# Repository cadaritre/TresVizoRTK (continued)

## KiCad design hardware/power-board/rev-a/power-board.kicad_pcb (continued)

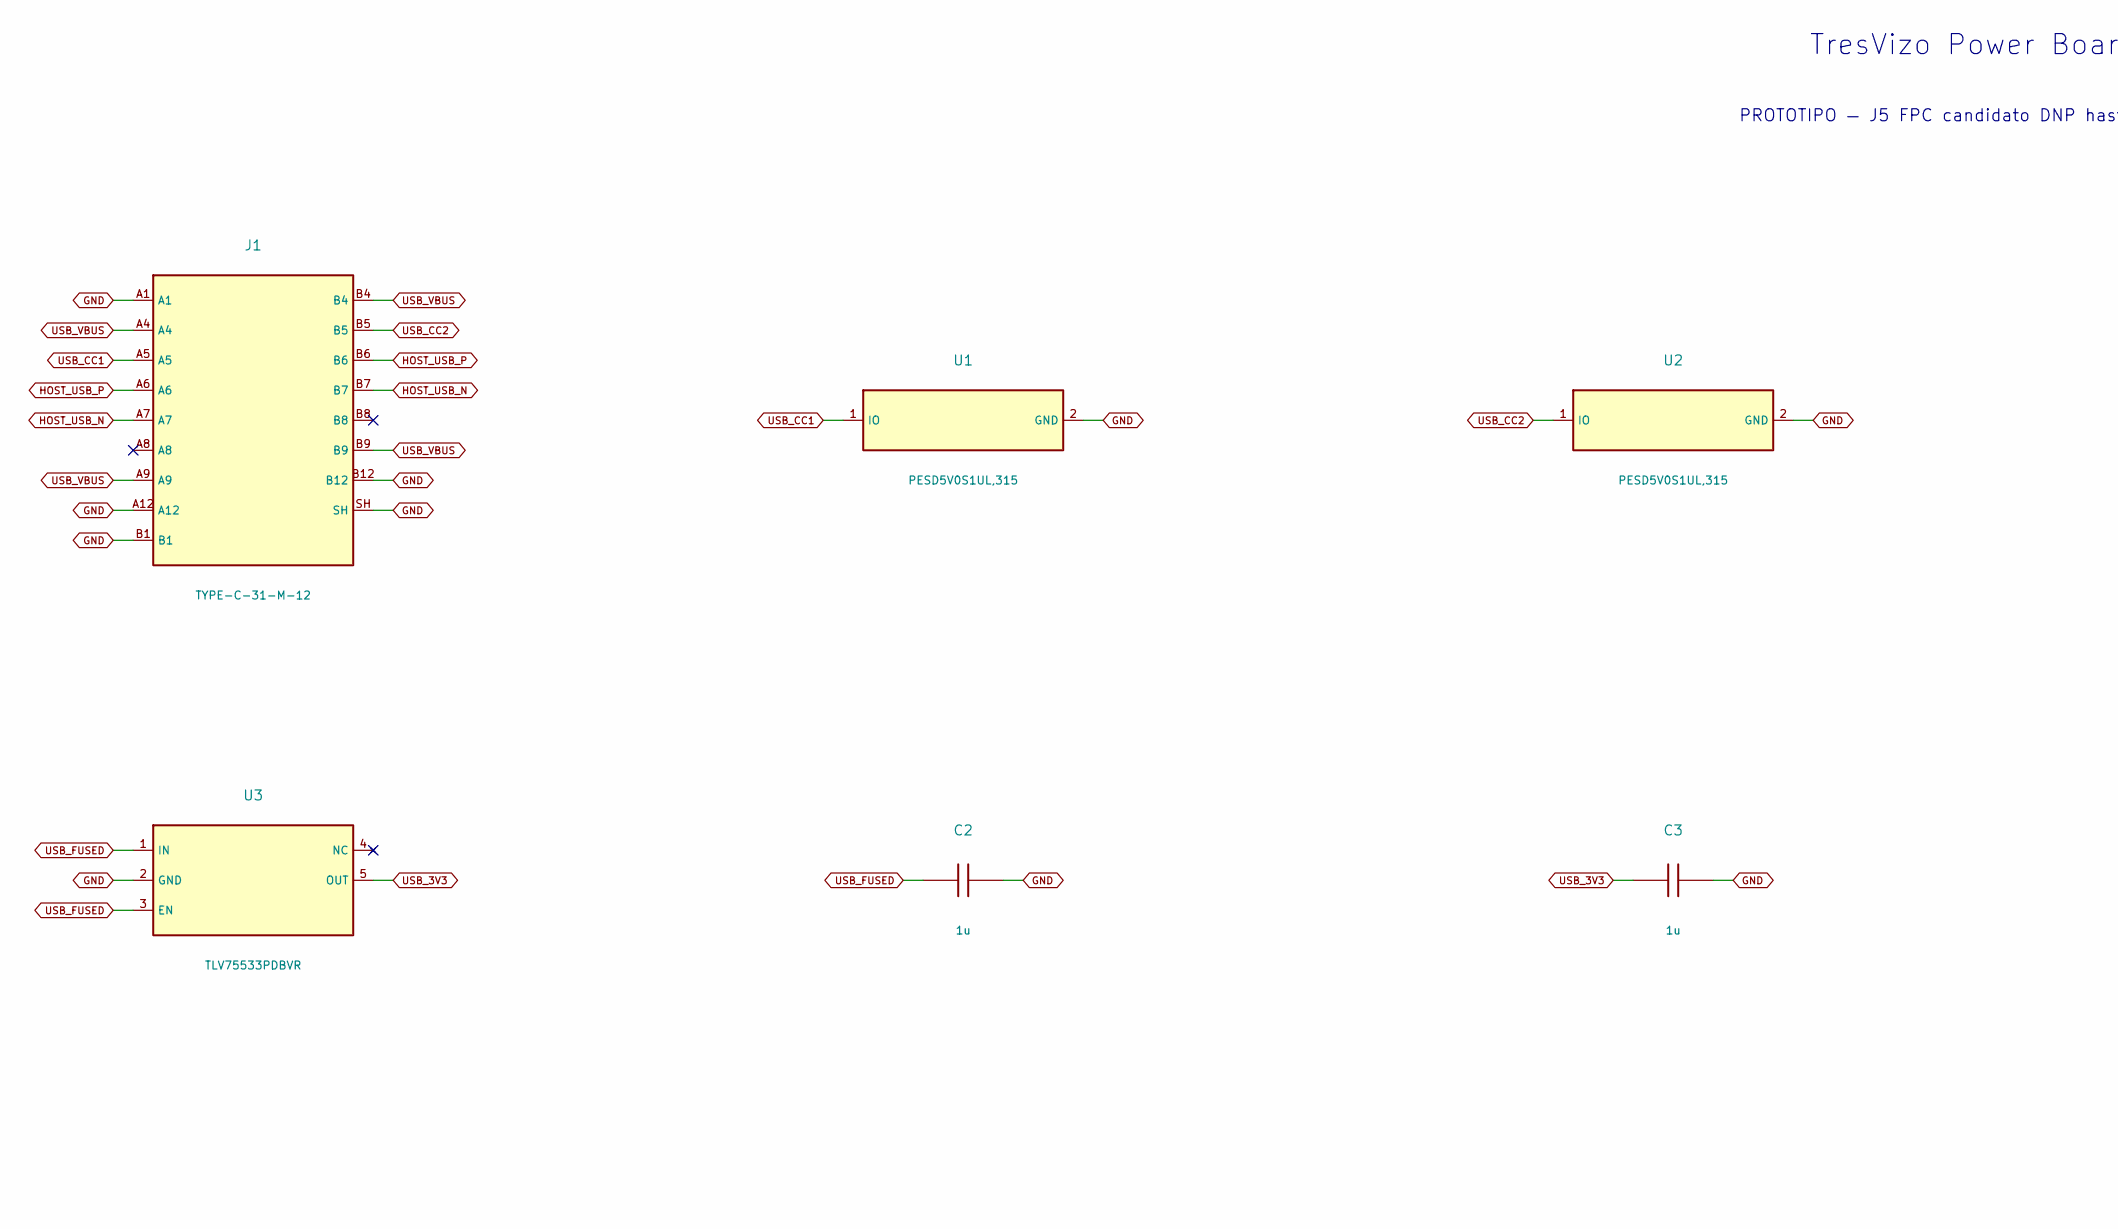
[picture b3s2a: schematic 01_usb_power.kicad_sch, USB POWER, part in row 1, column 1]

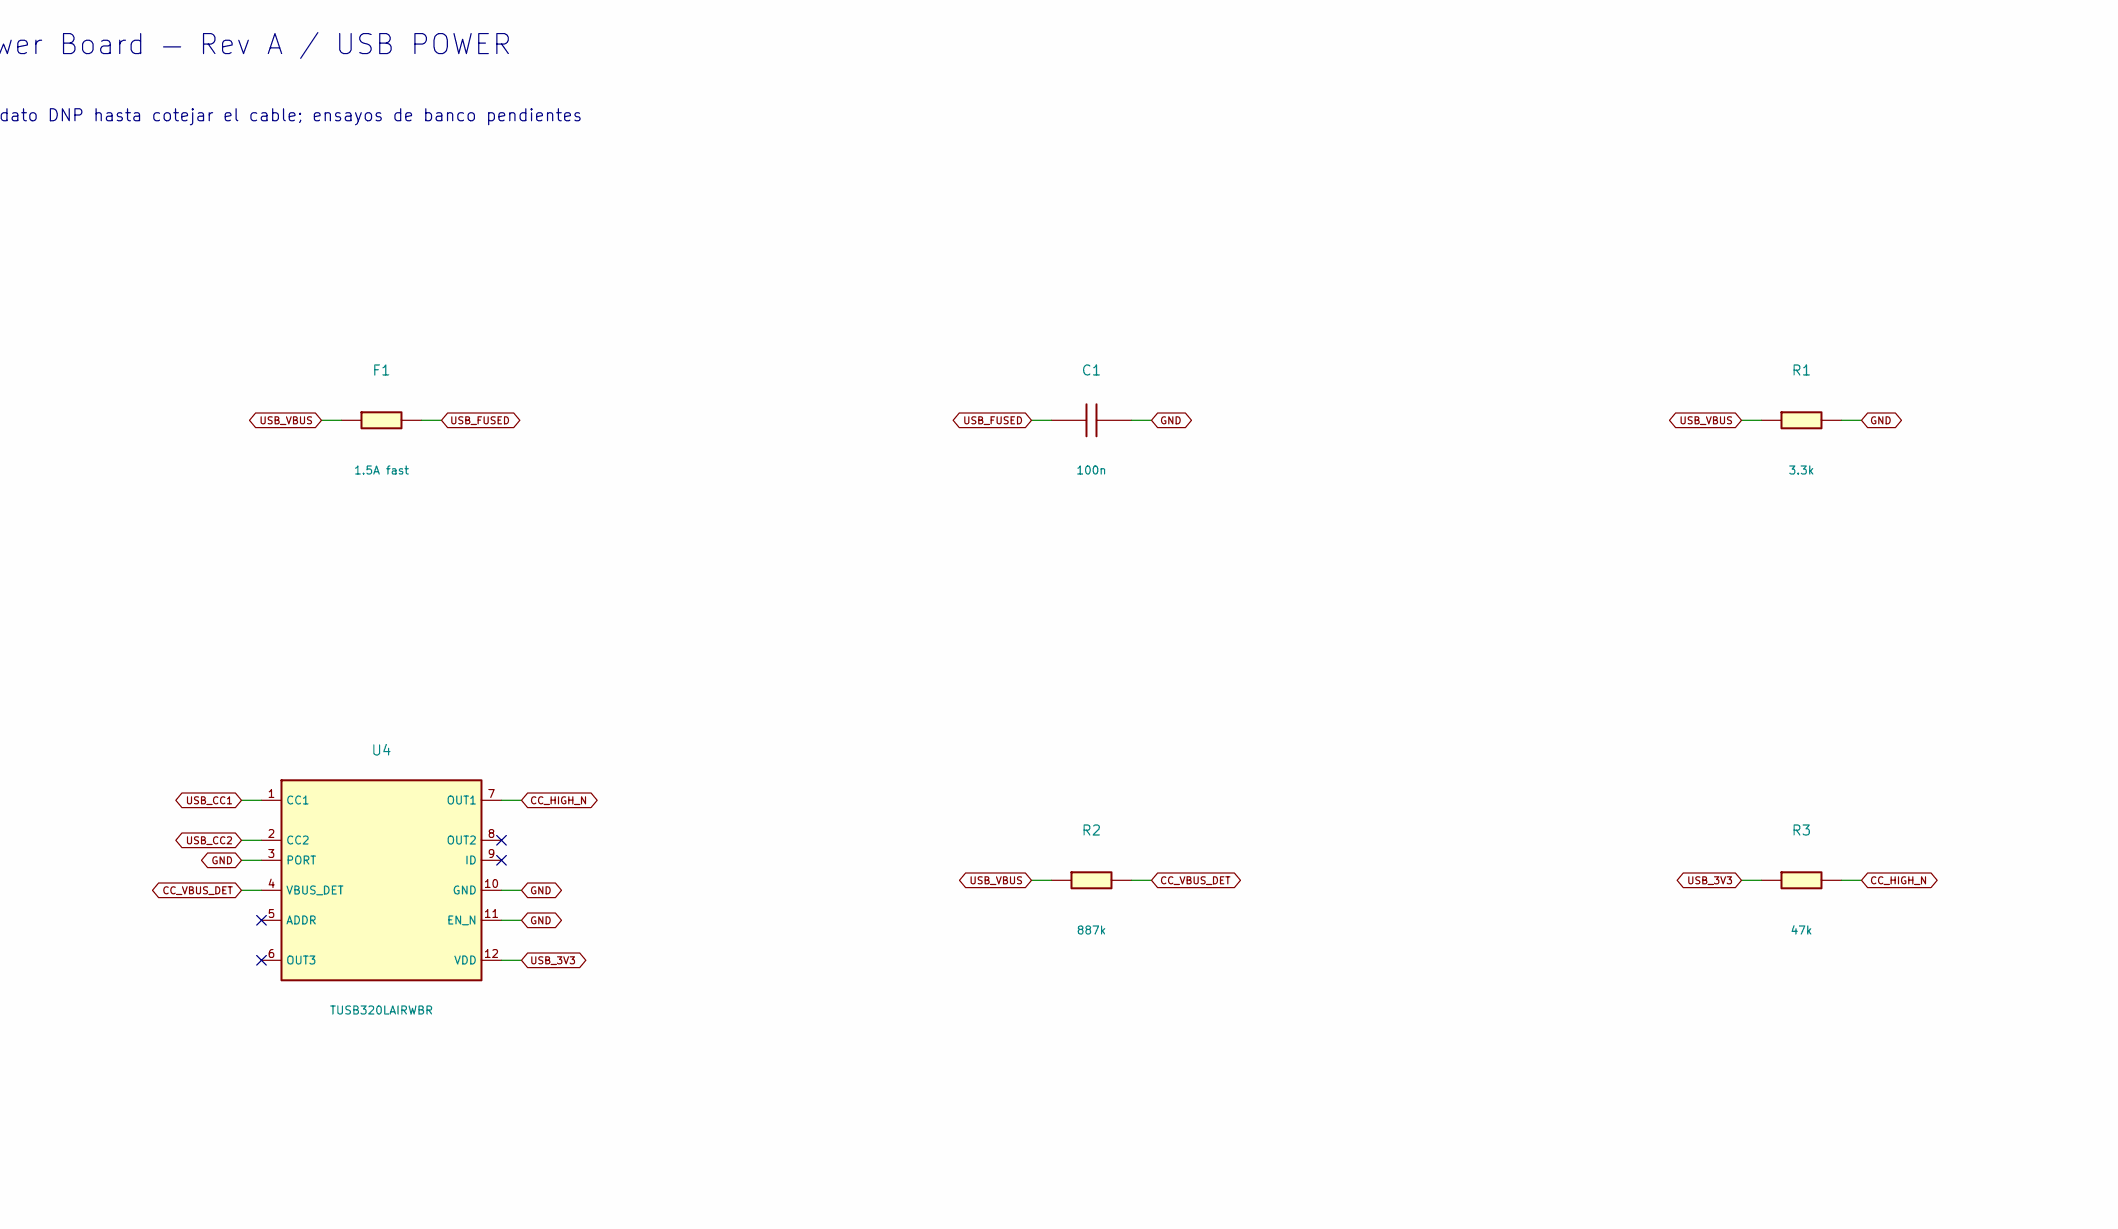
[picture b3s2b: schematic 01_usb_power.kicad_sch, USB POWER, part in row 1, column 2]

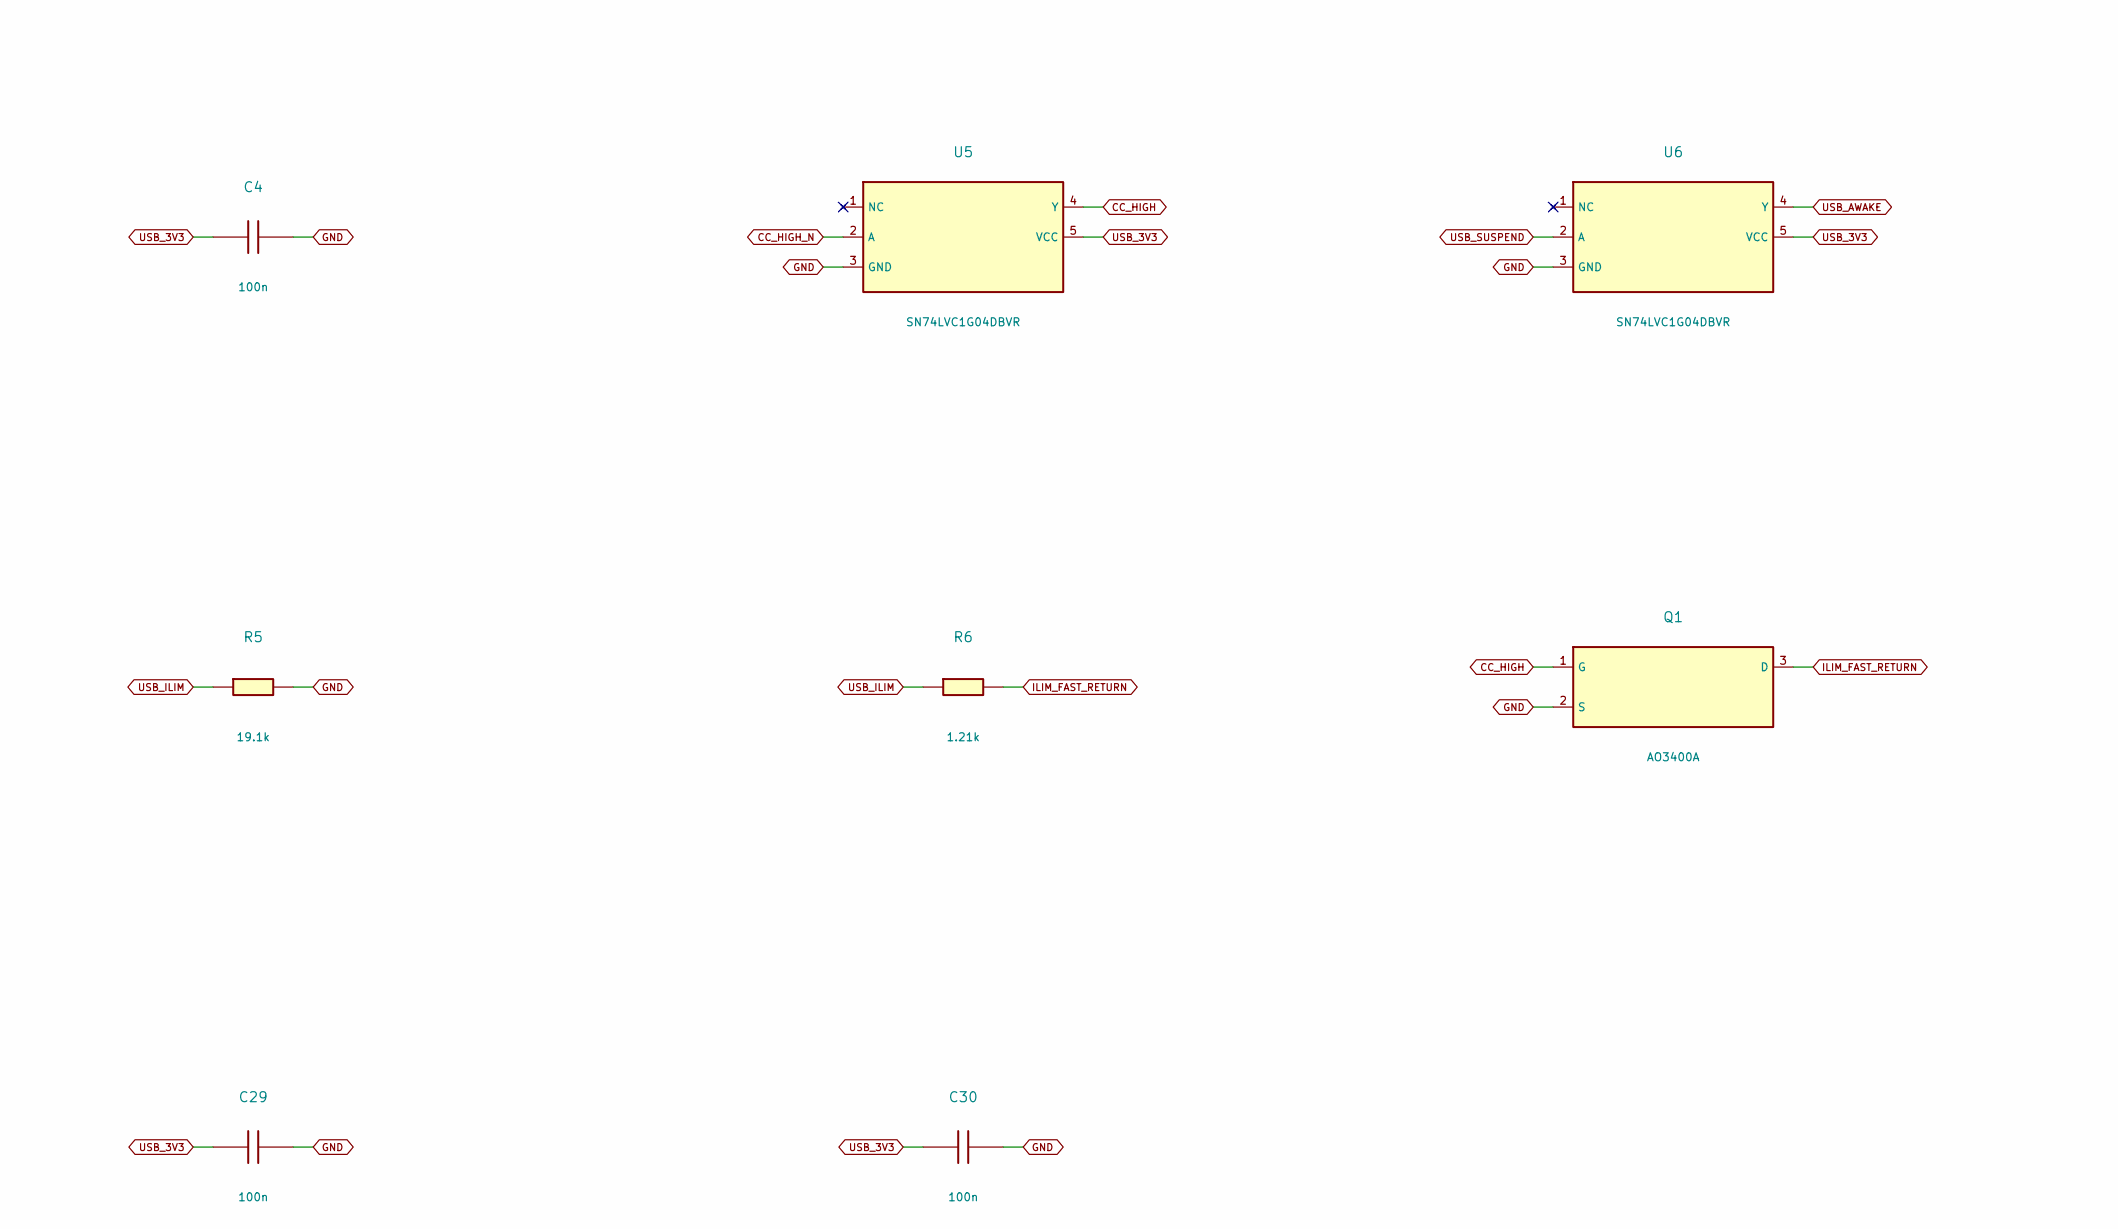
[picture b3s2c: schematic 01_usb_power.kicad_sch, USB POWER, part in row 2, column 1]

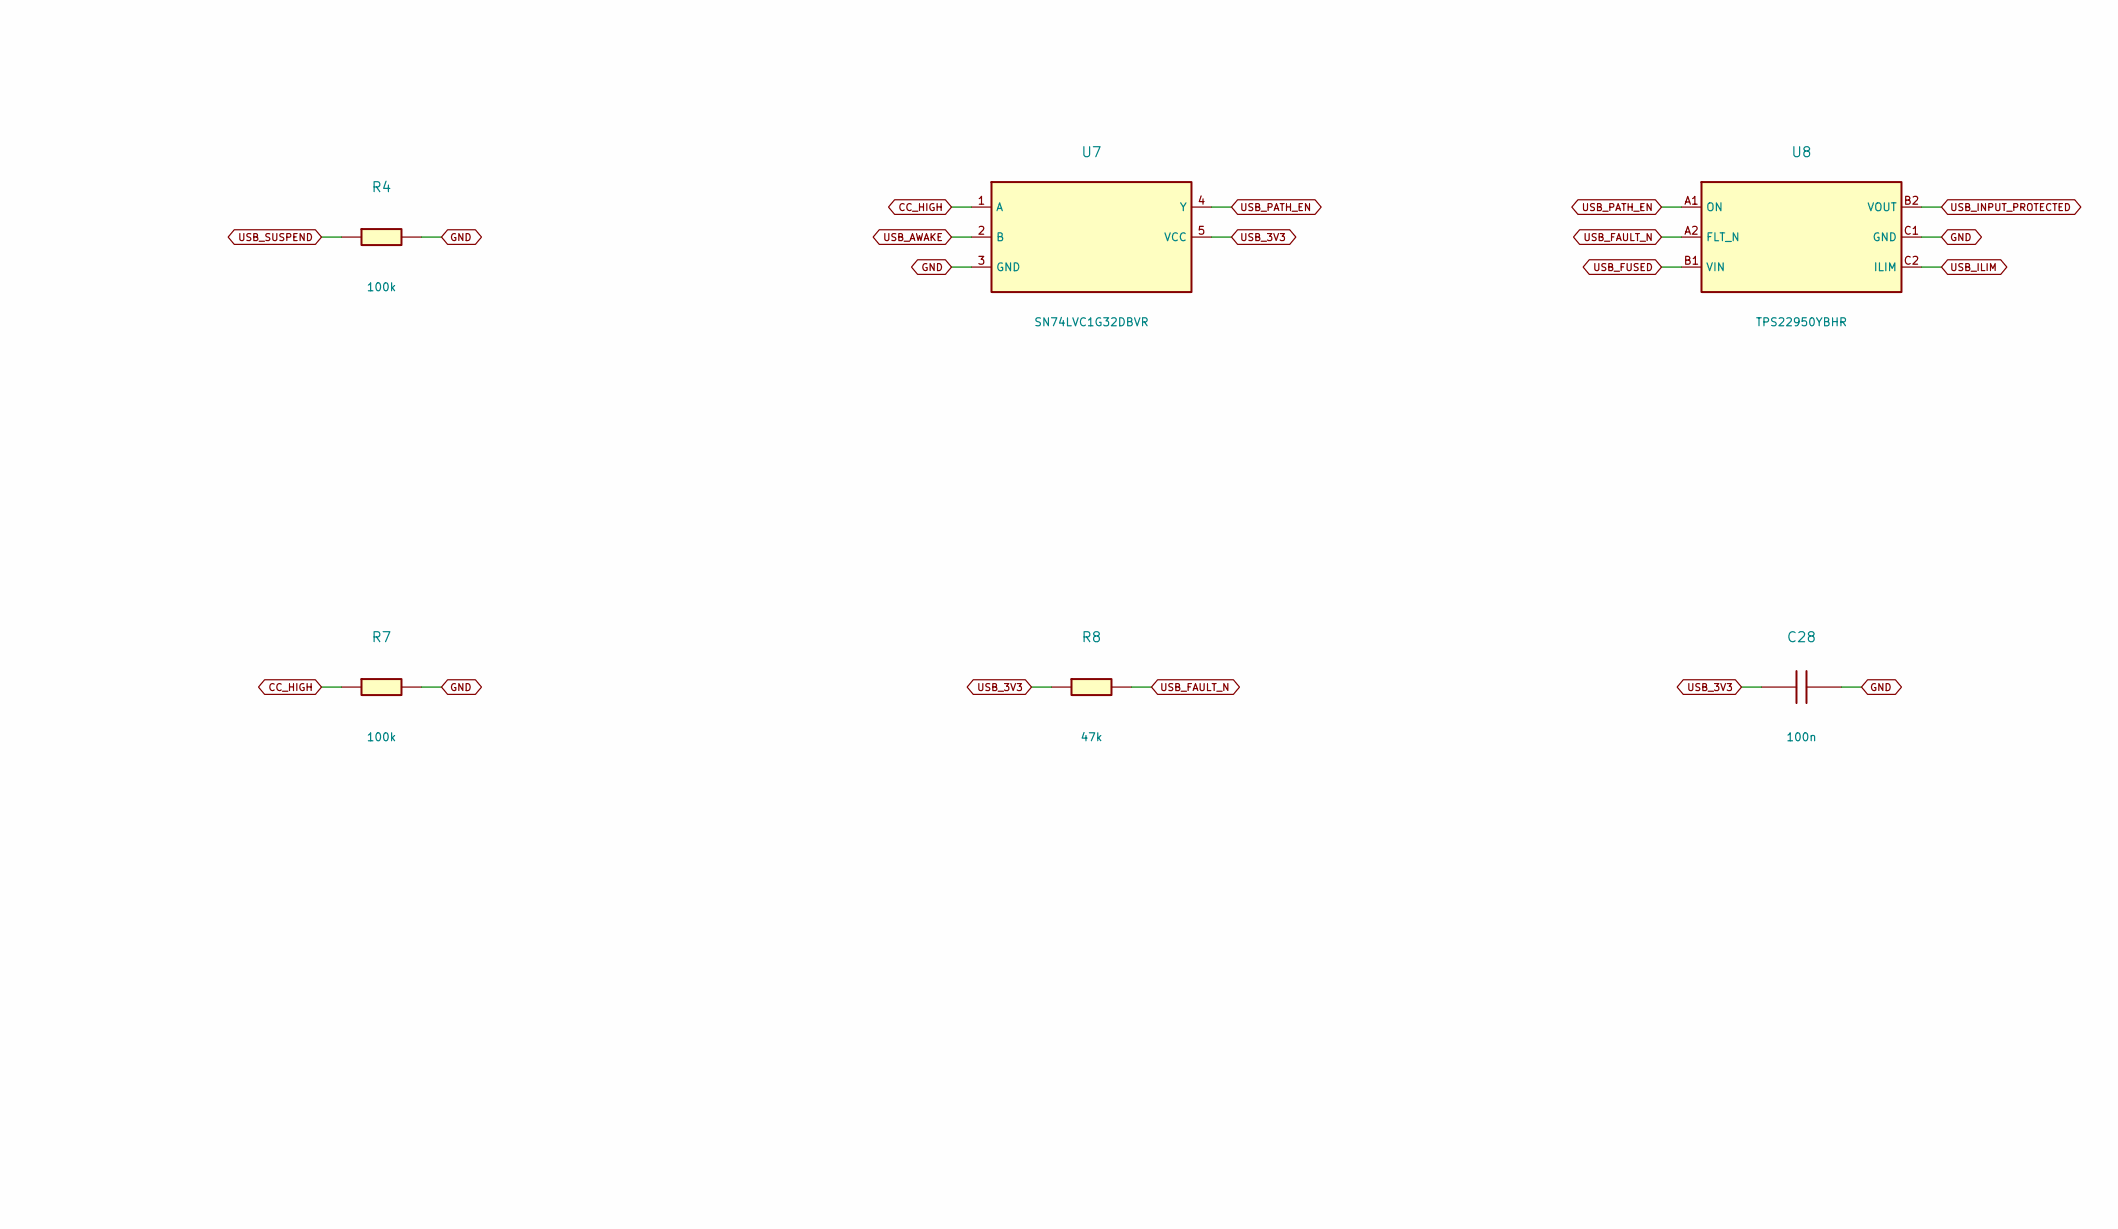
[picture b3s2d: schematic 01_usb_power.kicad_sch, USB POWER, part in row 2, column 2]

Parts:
C1, C4, C28, C29, C30: 100n; C_0603_1608Metric; MPN CC0603KRX7R9BB104
C2, C3: 1u; C_0603_1608Metric; MPN GRM188R71C105KA12D
F1: 1.5A fast; Fuse_1206_3216Metric; MPN 046601.5NRHF
J1: TYPE-C-31-M-12; USB_C_Receptacle_HRO_TYPE-C-31-M-12; MPN TYPE-C-31-M-12
Q1: AO3400A; SOT-23; MPN AO3400A
R1: 3.3k; R_0603_1608Metric; MPN RC0603FR-073K3L
R2: 887k; R_0603_1608Metric; MPN RC0603FR-07887KL
R3, R8: 47k; R_0603_1608Metric; MPN RC0603FR-0747KL
R4, R7: 100k; R_0603_1608Metric; MPN RC0603FR-07100KL
R5: 19.1k; R_0603_1608Metric; MPN RC0603FR-0719K1L
R6: 1.21k; R_0603_1608Metric; MPN RC0603FR-071K21L
U1, U2: PESD5V0S1UL,315; D_SOD-882; MPN PESD5V0S1UL,315
U3: TLV75533PDBVR; SOT-23-5; MPN TLV75533PDBVR
U4: TUSB320LAIRWBR; Texas_X2QFN-12_1.6x1.6mm_P0.4mm; MPN TUSB320LAIRWBR
U5, U6: SN74LVC1G04DBVR; SOT-23-5; MPN SN74LVC1G04DBVR
U7: SN74LVC1G32DBVR; SOT-23-5; MPN SN74LVC1G32DBVR
U8: TPS22950YBHR; TPS22950_YBH; MPN TPS22950YBHR

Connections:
CC_HIGH: Q1.1 (G), R7.1, U5.4 (Y), U7.1 (A)
CC_HIGH_N: R3.2, U4.7 (OUT1), U5.2 (A)
CC_VBUS_DET: R2.2, U4.4 (VBUS_DET)
GND: C1.2, C2.2, C3.2, C4.2, C28.2, C29.2, C30.2, J1.A1, J1.A12, J1.B1, J1.B12, J1.SH, Q1.2 (S), R1.2, R4.2, R5.2, R7.2, U1.2 (GND), U2.2 (GND), U3.2 (GND), U4.3 (PORT), U4.10 (GND), U4.11 (EN_N), U5.3 (GND), U6.3 (GND), U7.3 (GND), U8.C1 (GND); also elsewhere on the board
HOST_USB_N: J1.A7, J1.B7; also elsewhere on the board
HOST_USB_P: J1.A6, J1.B6; also elsewhere on the board
ILIM_FAST_RETURN: Q1.3 (D), R6.2
USB_3V3: C3.1, C4.1, C28.1, C29.1, C30.1, R3.1, R8.1, U3.5 (OUT), U4.12 (VDD), U5.5 (VCC), U6.5 (VCC), U7.5 (VCC); also elsewhere on the board
USB_AWAKE: U6.4 (Y), U7.2 (B)
USB_CC1: J1.A5, U1.1 (IO), U4.1 (CC1)
USB_CC2: J1.B5, U2.1 (IO), U4.2 (CC2)
USB_FAULT_N: R8.2, U8.A2 (FLT_N); also elsewhere on the board
USB_FUSED: C1.1, C2.1, F1.2, U3.1 (IN), U3.3 (EN), U8.B1 (VIN)
USB_ILIM: R5.1, R6.1, U8.C2 (ILIM)
USB_INPUT_PROTECTED: U8.B2 (VOUT); also elsewhere on the board
USB_PATH_EN: U7.4 (Y), U8.A1 (ON)
USB_SUSPEND: R4.1, U6.2 (A); also elsewhere on the board
USB_VBUS: F1.1, J1.A4, J1.A9, J1.B4, J1.B9, R1.1, R2.1; also elsewhere on the board

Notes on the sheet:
TresVizo Power Board — Rev A / USB POWER
PROTOTIPO — J5 FPC candidato DNP hasta cotejar el cable; ensayos de banco pendientes

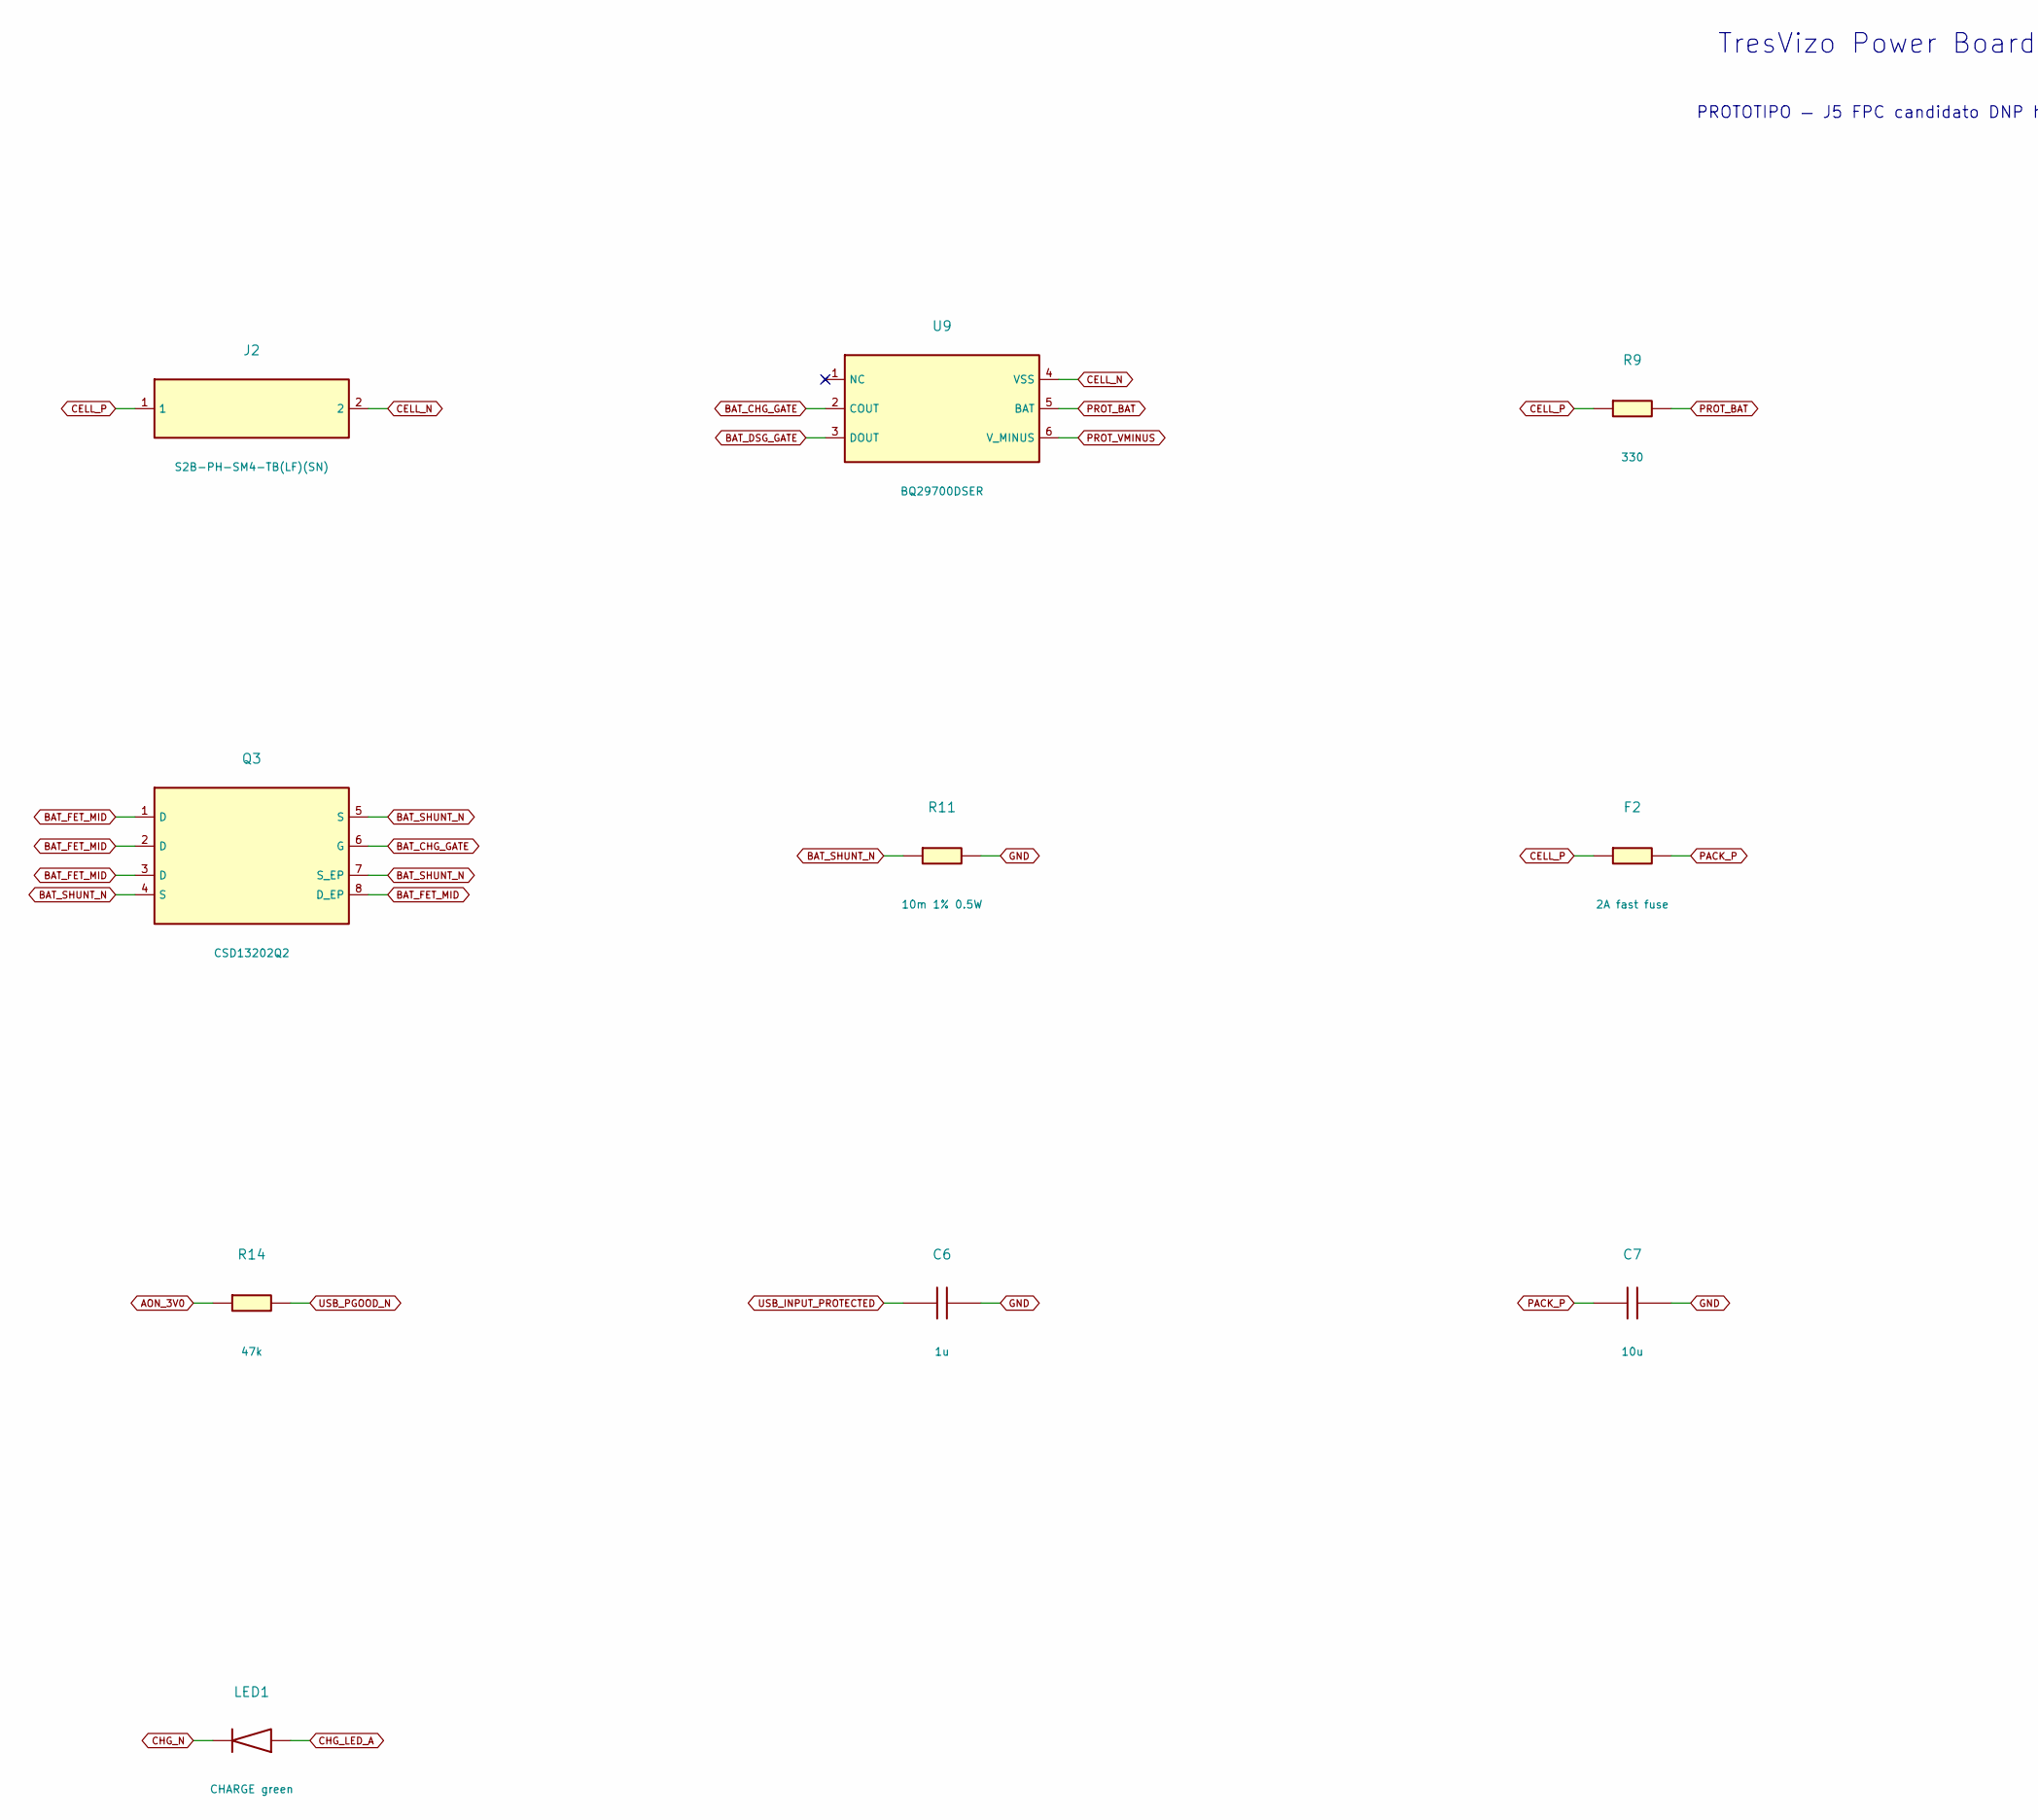
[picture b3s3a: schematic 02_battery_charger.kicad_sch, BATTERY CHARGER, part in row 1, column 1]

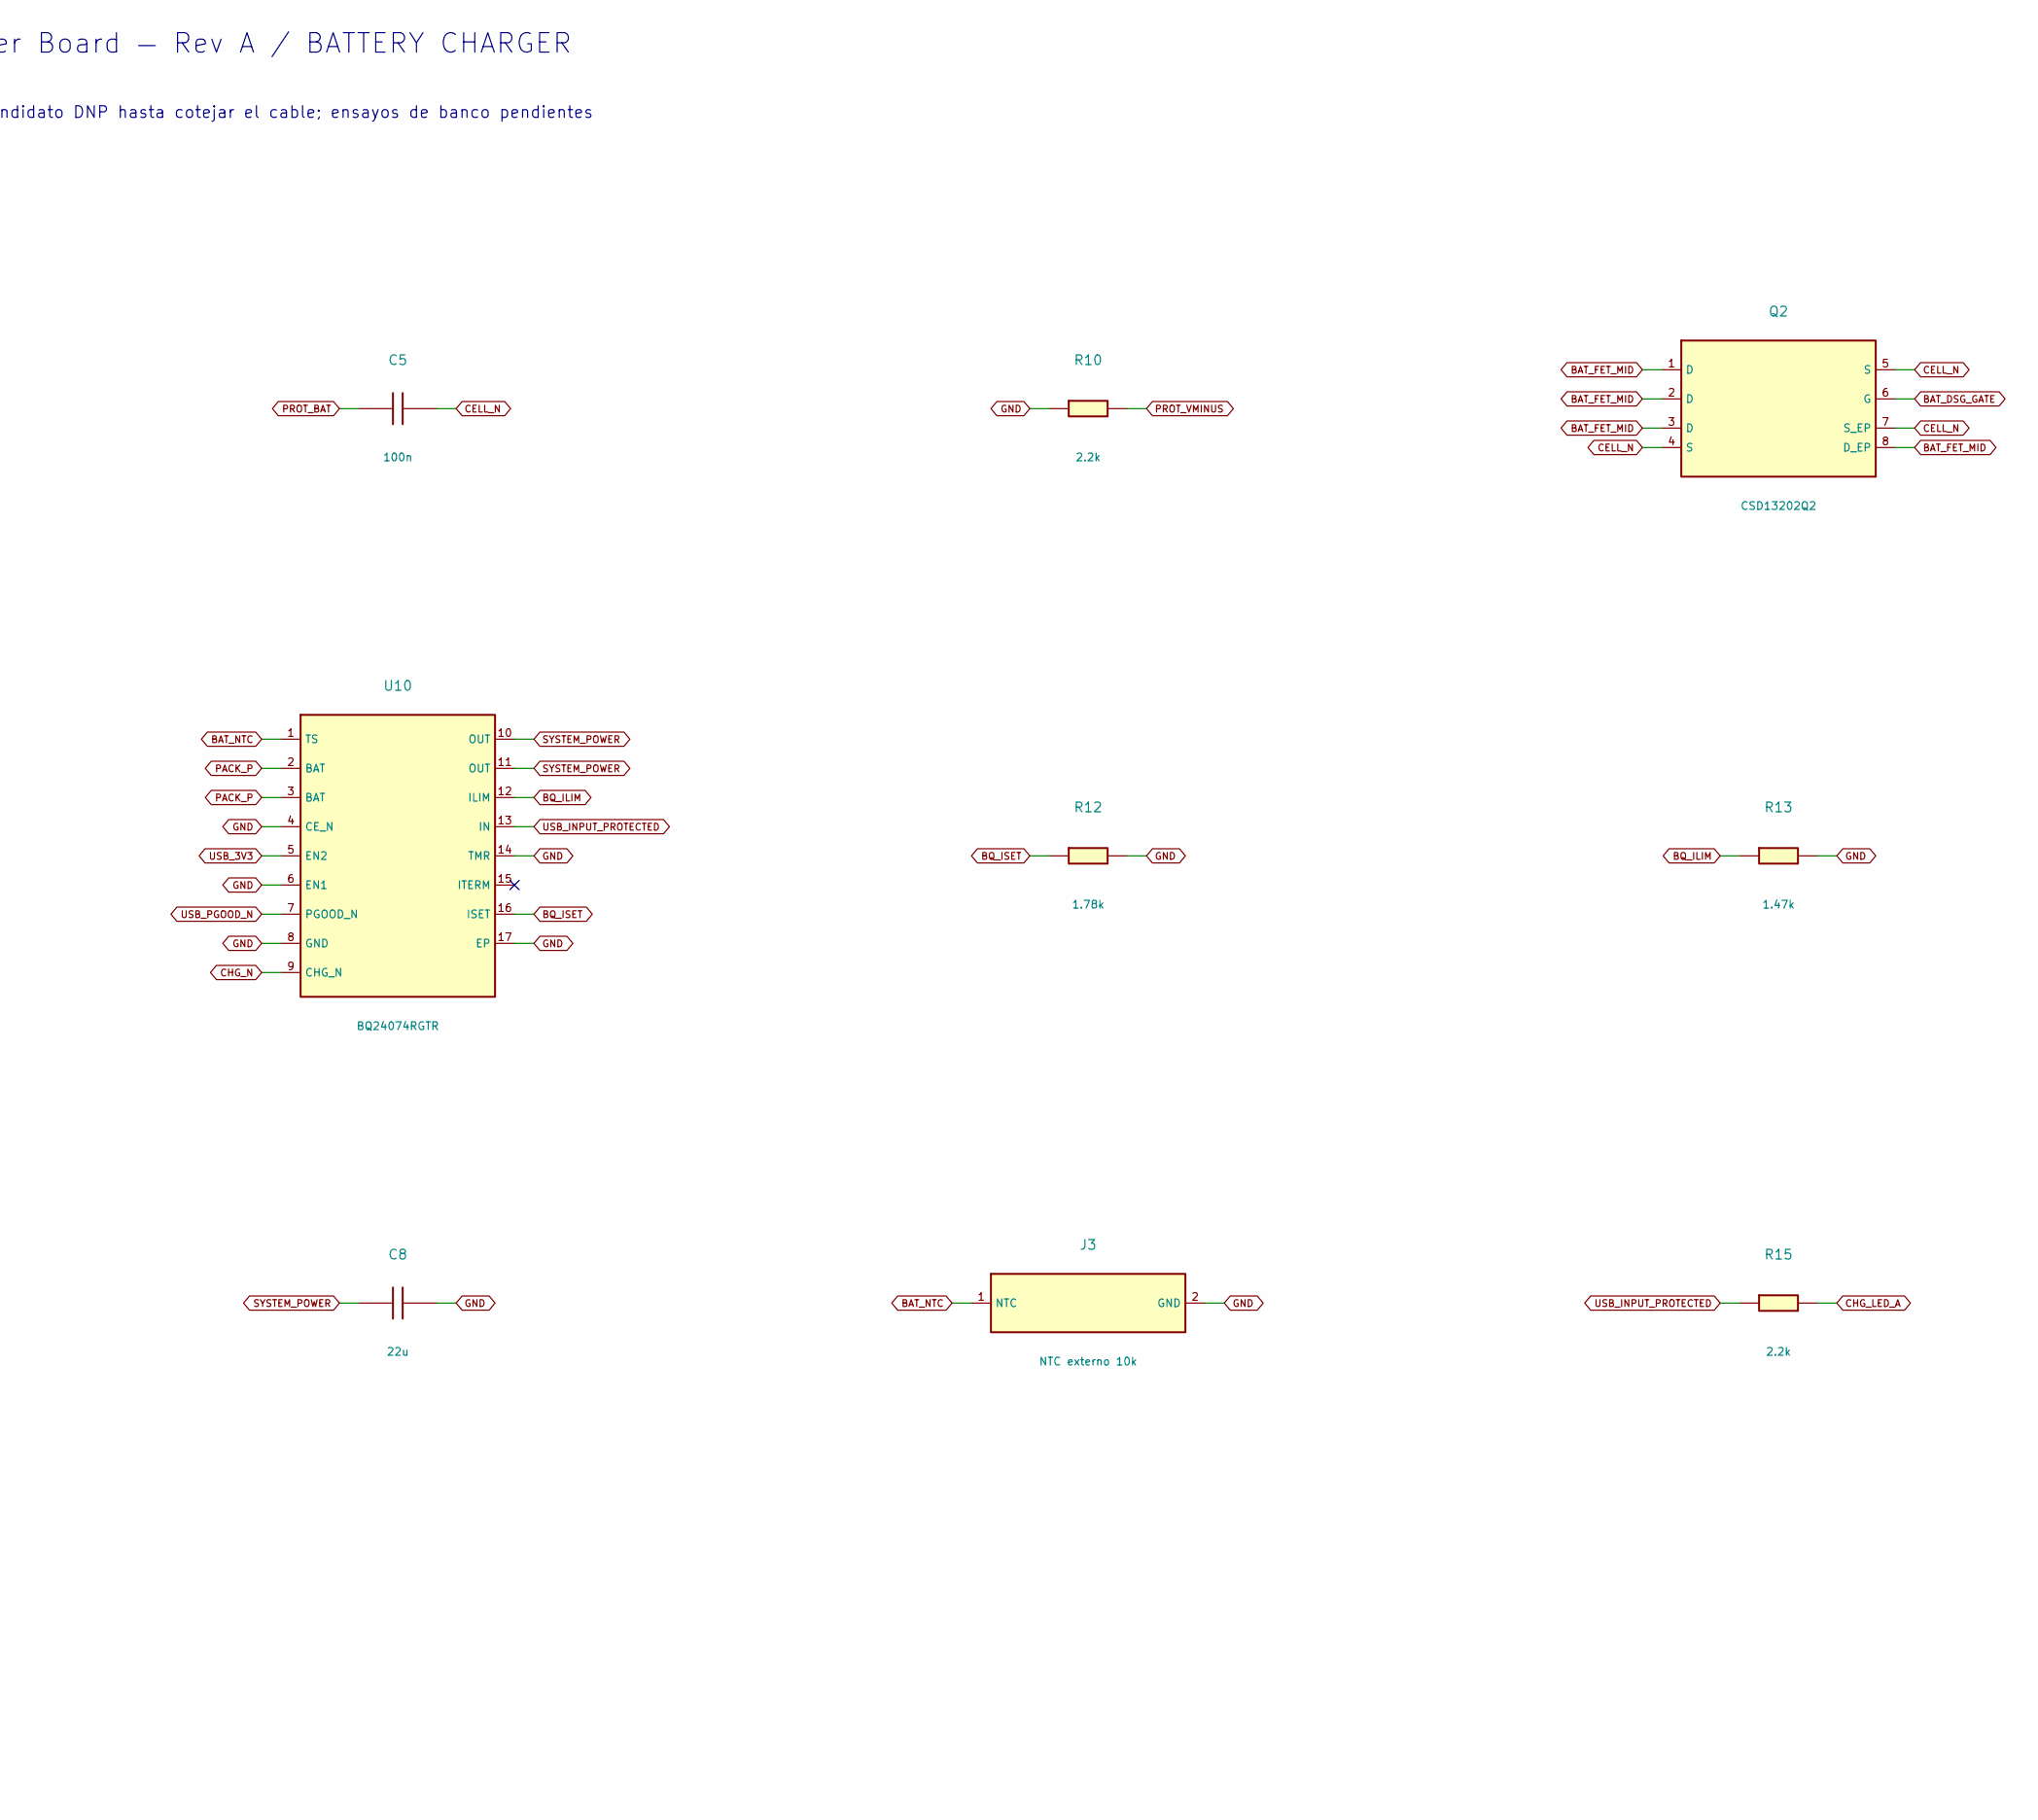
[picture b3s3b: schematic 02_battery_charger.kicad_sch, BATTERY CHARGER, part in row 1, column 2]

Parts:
C5: 100n; C_0603_1608Metric; MPN CC0603KRX7R9BB104
C6: 1u; C_0603_1608Metric; MPN GRM188R71C105KA12D
C7: 10u; C_0805_2012Metric; MPN GRM21BR71A106KE51L
C8: 22u; C_1206_3216Metric; MPN GRM31CR71A226KE15L
F2: 2A fast fuse; Fuse_1206_3216Metric; MPN 0466002.NRHF
J2: S2B-PH-SM4-TB(LF)(SN); JST_PH_S2B-PH-SM4-TB_1x02-1MP_P2.00mm_Horizontal; MPN S2B-PH-SM4-TB(LF)(SN)
J3: NTC externo 10k; JST_SH_SM02B-SRSS-TB_1x02-1MP_P1.00mm_Horizontal; MPN SM02B-SRSS-TB(LF)(SN)
LED1: CHARGE green; LED_0603_1608Metric; MPN LTST-C190KGKT
Q2, Q3: CSD13202Q2; MPN CSD13202Q2
R9: 330; R_0603_1608Metric; MPN RC0603FR-07330RL
R10, R15: 2.2k; R_0603_1608Metric; MPN RC0603FR-072K2L
R11: 10m 1% 0.5W; R_1206_3216Metric; MPN WSL1206R0100FEA
R12: 1.78k; R_0603_1608Metric; MPN RC0603FR-071K78L
R13: 1.47k; R_0603_1608Metric; MPN RC0603FR-071K47L
R14: 47k; R_0603_1608Metric; MPN RC0603FR-0747KL
U9: BQ29700DSER; WSON-6_1.5x1.5mm_P0.5mm; MPN BQ29700DSER
U10: BQ24074RGTR; VQFN-16-1EP_3x3mm_P0.5mm_EP1.68x1.68mm; MPN BQ24074RGTR

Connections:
AON_3V0: R14.1; also elsewhere on the board
BAT_CHG_GATE: Q3.6 (G), U9.2 (COUT)
BAT_DSG_GATE: Q2.6 (G), U9.3 (DOUT)
BAT_FET_MID: Q2.1 (D), Q2.2 (D), Q2.3 (D), Q2.8 (D_EP), Q3.1 (D), Q3.2 (D), Q3.3 (D), Q3.8 (D_EP)
BAT_NTC: J3.1 (NTC), U10.1 (TS)
BAT_SHUNT_N: Q3.4 (S), Q3.5 (S), Q3.7 (S_EP), R11.1
BQ_ILIM: R13.1, U10.12 (ILIM)
BQ_ISET: R12.1, U10.16 (ISET)
CELL_N: C5.2, J2.2, Q2.4 (S), Q2.5 (S), Q2.7 (S_EP), U9.4 (VSS)
CELL_P: F2.1, J2.1, R9.1
CHG_LED_A: LED1.2 (A), R15.2
CHG_N: LED1.1 (K), U10.9 (CHG_N)
GND: C6.2, C7.2, C8.2, J3.2 (GND), R10.1, R11.2, R12.2, R13.2, U10.4 (CE_N), U10.6 (EN1), U10.8 (GND), U10.14 (TMR), U10.17 (EP); also elsewhere on the board
PACK_P: C7.1, F2.2, U10.2 (BAT), U10.3 (BAT); also elsewhere on the board
PROT_BAT: C5.1, R9.2, U9.5 (BAT)
PROT_VMINUS: R10.2, U9.6 (V_MINUS)
SYSTEM_POWER: C8.1, U10.10 (OUT), U10.11 (OUT); also elsewhere on the board
USB_3V3: U10.5 (EN2); also elsewhere on the board
USB_INPUT_PROTECTED: C6.1, R15.1, U10.13 (IN); also elsewhere on the board
USB_PGOOD_N: R14.2, U10.7 (PGOOD_N)

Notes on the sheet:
TresVizo Power Board — Rev A / BATTERY CHARGER
PROTOTIPO — J5 FPC candidato DNP hasta cotejar el cable; ensayos de banco pendientes
